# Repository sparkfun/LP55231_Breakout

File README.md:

SparkFun LP55231 LED Driver Breakout
========================================

[*SparkFun LP55231 LED Driver Breakout (BOB-13884)*](https://www.sparkfun.com/products/13884)

Breakout Board for the Texas Instruments LP55231 9-channel LED driver IC, with three onboard RGB LEDs.

Repository Contents
-------------------

* **/Documentation** - LP55231 data sheet.
* **/Enclosure** - Enclosure files
* **/Firmware** - Some test sketches.  For more useful sketches, please refer to the [LP55231 Arduino Library](https://github.com/sparkfun/SparkFun_LP55231_Arduino_Library)
* **/Hardware** - Eagle design files (.brd, .sch)
* **/Libraries** - work-in-progress libraries.  Release library has [its own repository](https://github.com/sparkfun/SparkFun_LP55231_Arduino_Library)
* **/Production** - Production panel files (.brd)
* **/Software** - Related software for the <PRODUCT NAME>

Documentation
--------------
* **[Library](https://github.com/sparkfun/SparkFun_LP55231_Arduino_Library)** - Arduino library for the LP55231 breakout board.
* **[Hookup Guide](https://learn.sparkfun.com/tutorials/lp55231-breakout-board-hookup-guide)** - Basic hookup guide for the LP55231 breakout.
* **[SparkFun Fritzing repo](https://github.com/sparkfun/Fritzing_Parts)** - Fritzing diagrams for SparkFun products.
* **[SparkFun 3D Model repo](https://github.com/sparkfun/3D_Models)** - 3D models of SparkFun products.
* **[SparkFun Graphical Datasheets](https://github.com/sparkfun/Graphical_Datasheets)** -Graphical Datasheets for various SparkFun products.

Product Versions
----------------
* [BOB-13884](https://www.sparkfun.com/products/13884)- Storefront page where you can purchase the LP55231 breakout board.

Version History
---------------
* [7303a14bc03e4db13bc608a852c81e9e0ca2a5a7](https://github.com/sparkfun/LP55231_Breakout/commit/7303a14bc03e4db13bc608a852c81e9e0ca2a5a7) - Initial release version.

License Information
-------------------

This product is _**open source**_!

Please review the LICENSE.md file for license information.

If you have any questions or concerns on licensing, please contact techsupport@sparkfun.com.

Distributed as-is; no warranty is given.

- Your friends at SparkFun.

_<COLLABORATION CREDIT>_

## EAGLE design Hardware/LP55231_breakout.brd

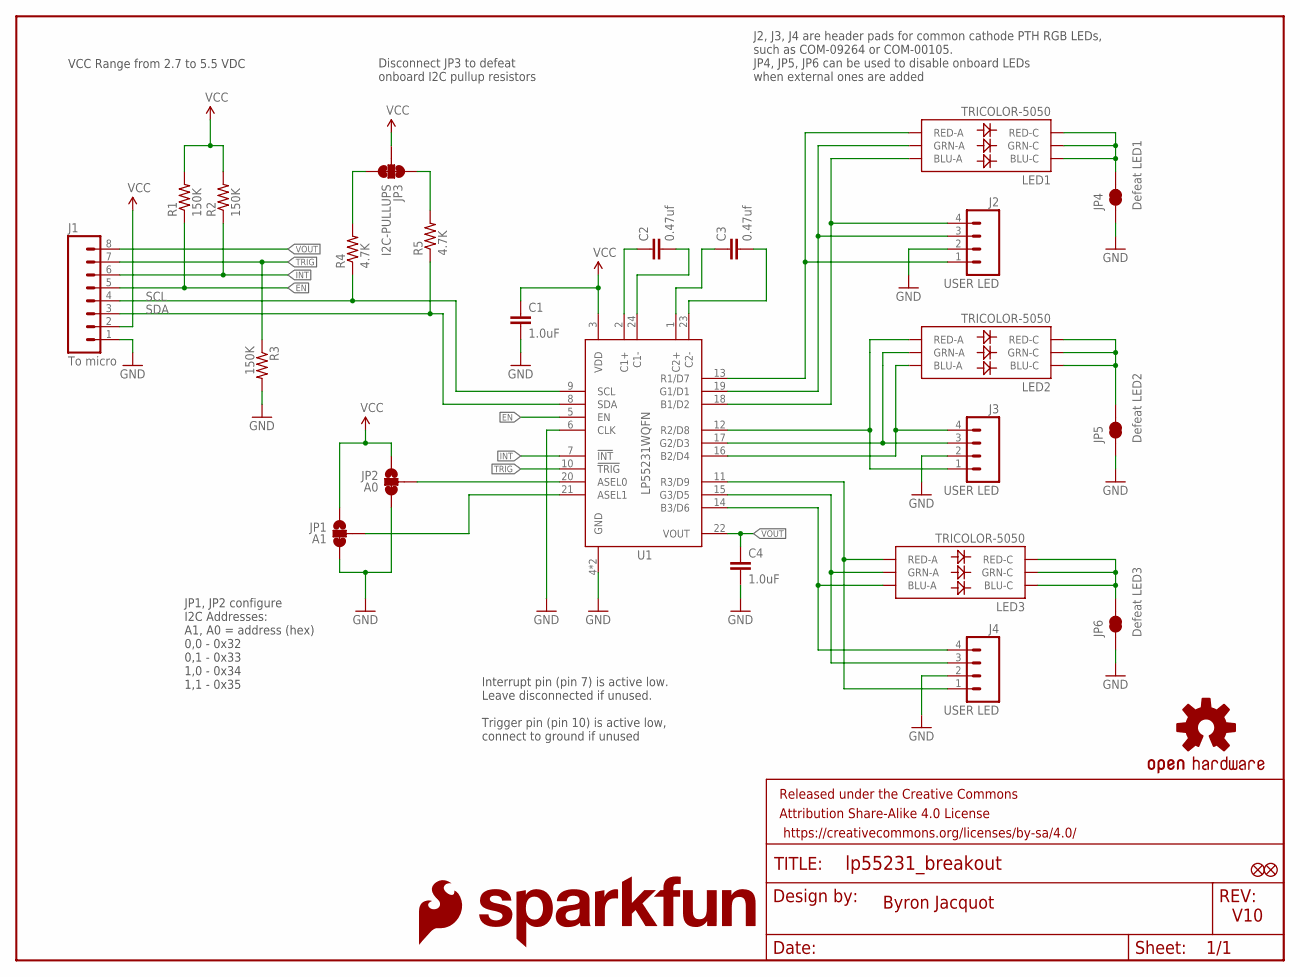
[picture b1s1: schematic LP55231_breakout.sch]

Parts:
C1, C4: 1.0uF; 0603-CAP
C2, C3: 0.47uf; 0603-CAP
FD1, FD2: FIDUCIALUFIDUCIAL; MICRO-FIDUCIAL
FRAME1: FRAME-LETTER; CREATIVE_COMMONS
J1: To micro; 1X08_NO_SILK
J2, J3, J4: USER LED; 1X04_NO_SILK_ALL_ROUND
JP1: A1; PAD-JUMPER-3-2OF3_NC_BY_TRACE_YES_SILK_FULL_BOX
JP2: A0; PAD-JUMPER-3-2OF3_NC_BY_TRACE_YES_SILK_FULL_BOX
JP3: I2C-PULLUPS; PAD-JUMPER-3-3OF3_NC_BY_TRACE_YES_SILK_FULL_BOX
JP4: Defeat LED1; PAD-JUMPER-2-NC_BY_TRACE_NO_SILK
JP5: Defeat LED2; PAD-JUMPER-2-NC_BY_TRACE_NO_SILK
JP6: Defeat LED3; PAD-JUMPER-2-NC_BY_TRACE_NO_SILK
LED1, LED2, LED3: TRICOLOR-5050; LED-TRICOLOR-5050
LOGO1: SFE_LOGO_FLAME.1_INCH; SFE_LOGO_FLAME_.1
LOGO2: SFE_LOGO_NAME.1_INCH; SFE_LOGO_NAME_.1
LOGO3: OSHW-LOGOS; OSHW-LOGO-S
R1, R2, R3: 150K; 0603-RES
R4, R5: 4.7K; 0603-RES
U1: LP55231WQFN; WQFN-24

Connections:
ADDR0: JP2.2, U1.20 (ASEL0)
ADDR1: JP1.2, U1.21 (ASEL1)
B1: J2.4, LED1.3 (BLU-A), U1.18 (B1/D2)
B2: J3.4, LED2.3 (BLU-A), U1.16 (B2/D4)
B3: J4.4, LED3.3 (BLU-A), U1.14 (B3/D6)
EN: J1.5, R1.1, U1.5 (EN)
G1: J2.3, LED1.1 (GRN-A), U1.19 (G1/D1)
G2: J3.3, LED2.1 (GRN-A), U1.17 (G2/D3)
G3: J4.3, LED3.1 (GRN-A), U1.15 (G3/D5)
GND: C1.2, C4.2, J1.1, J2.2, J3.2, J4.2, JP1.3, JP2.3, JP4.1, JP5.1, JP6.1, R3.2, U1.4 (GND), U1.6 (CLK), U1.EP (GND)
INT: J1.6, R2.1, U1.7 (!INT)
unnamed: JP6.2, LED3.4 (BLU-C), LED3.5 (RED-C), LED3.6 (GRN-C)
unnamed: JP5.2, LED2.4 (BLU-C), LED2.5 (RED-C), LED2.6 (GRN-C)
unnamed: JP4.2, LED1.4 (BLU-C), LED1.5 (RED-C), LED1.6 (GRN-C)
unnamed: C2.1, U1.2 (C1+)
unnamed: C2.2, U1.24 (C1-)
unnamed: C3.1, U1.1 (C2+)
unnamed: C3.2, U1.23 (C2-)
unnamed: JP3.1, R5.2
unnamed: JP3.3, R4.2
R1: J2.1, LED1.2 (RED-A), U1.13 (R1/D7)
R2: J3.1, LED2.2 (RED-A), U1.12 (R2/D8)
R3: J4.1, LED3.2 (RED-A), U1.11 (R3/D9)
SCL: J1.4, R4.1, U1.9 (SCL)
SDA: J1.3, R5.1, U1.8 (SDA)
TRIG: J1.7, R3.1, U1.10 (!TRIG)
VCC: C1.1, J1.2, JP1.1, JP2.1, JP3.2, R1.2, R2.2, U1.3 (VDD)
VOUT: C4.1, J1.8, U1.22 (VOUT)

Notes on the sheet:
Byron Jacquot
V10
VCC Range from 2.7 to 5.5 VDC
JP1, JP2 configure I2C Addresses: A1, A0 = address (hex) 0,0 - 0x32 0,1 - 0x33 1,0 - 0x34 1,1 - 0x35
J2, J3, J4 are header pads for common cathode PTH RGB LEDs, such as COM-09264 or COM-00105. JP4, JP5, JP6 can be used to disable onboard LEDs when external ones are added
Disconnect JP3 to defeat onboard I2C pullup resistors
Interrupt pin (pin 7) is active low. Leave disconnected if unused. Trigger pin (pin 10) is active low, connect to ground if unused

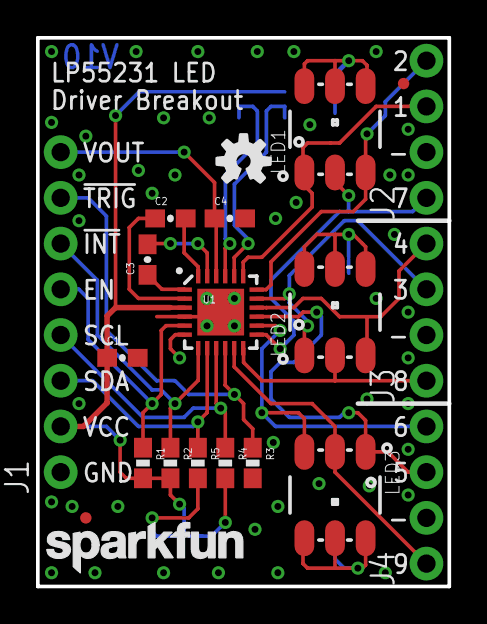
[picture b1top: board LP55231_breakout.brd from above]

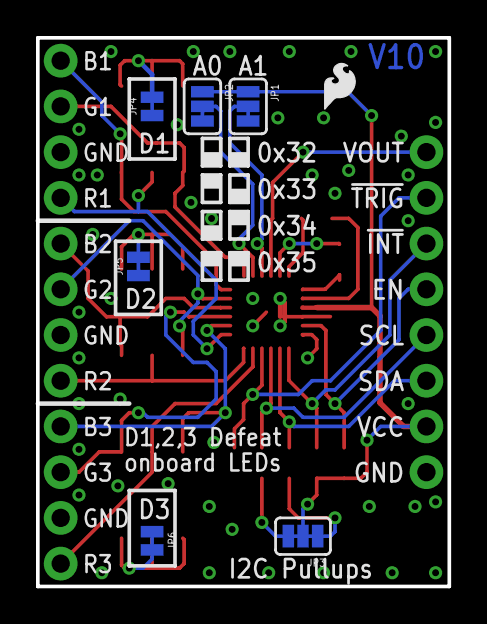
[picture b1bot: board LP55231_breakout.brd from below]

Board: 4 copper layers, 22.9 x 30.5 mm, 29 parts (7 on the bottom side), 28 nets.

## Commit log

2016-03-14 Adding repo boilerplate.
2016-03-15 Initial design files.
    Library, schem and PCB, all WIP.
2016-03-24 PCB Work in progress.
2016-03-25 Incremental PCB routing checkin.
    Eagle crashed and I'm paranoid now.
2016-03-25 Routing approaching completion.
2016-03-31 Prepping for review.
    BOM created, checklist scrubbed.
2016-04-04 Straight out of QFN.
    Fewer bends & kinks.
2016-04-04 Fixing review issues.
    -Fiducial moved from under silk.
    -Swapped numbering of LED's 2 & 3.
2016-04-27 Adding datasheet and test sketch.
2016-04-27 Adding a note for I2C r/w info.
2016-04-28 Hardware is starting to talk.
    Not sophisticated, but minimally functional.
2016-04-28 More success...
    ...I've got a little program running in one of the execution engines.
2016-04-28 Execution engine & output mapping
    cumbersome but functional!
2016-05-03 Working on library class
2016-05-04 Incremental changes.
    Adding software library features to support hardware testing.
    Trigger and interrupt pins are working.
2016-05-06 Updates to PCB after testing.
    Preparing for second round of prototypes.
2016-05-09 Updates after group review.
    Addressing things in issue #3:
    -bump version number
    -Add silk indicating flooded/empty configuration on A0/A1
    -space out passives on front (check tkeepout)
    -remove extra junction dot between 150k res and Vcc on schematic
2016-05-10 Checklist updates for proto round 2.
2016-05-11 Checklist review issues
    Numbering of jumpers vs. comments got mismatched.
    Now fixed.
2016-06-15 Fixing RGB assignments of first LED.
2016-06-21 Rolling version number
    From V02 to V03.
2016-06-22 Changes post-review.
    "G" becomes "-", to prevent confusion with "6".
    Angle voliation inside LED pad remedied.
2016-06-24 Clarifying one schematic note.
2016-07-29 Adding some hardware test sketches.
2016-08-05 Adding micro->driver trigger example.
2016-08-16 Adding sketches for Interrupt and output triggering.
2016-08-16 Adding sample sketch example of bidirectional trigger.
    Got the pin direction question answered.
    There's an external pull down that tugs the line when the internal pulup
    gets defeated.
2016-08-17 Adding start on Arduino Library...
    Basics are working, but parallel engines, program verification are not.
2016-08-18 Program verification is working.
    On a single page, at least.
    Setting PC is still problematic.
2016-08-18 Adding multi-page write/verify.
2016-08-19 Making updates after group & checklist reviews.
    Rolling version # to V10.
2016-08-22 Improvements to parallel engines.
    Takes careful manipulation of memory.
    PC & branches are done relative to program entry point, not absolute
    instruction location.
2016-08-23 More integration tests
    Temperature reading
    ADC for outputs and voltages.
2016-08-25 Adding auto-larson-scanner
    Found & fixed pervasive error in page programming.
    Added larson scanner with large mapping table.
2016-10-06 Reorganizing libraries a bit.
    Adding multi-page programming, and Int-to-GPO access.
2016-10-06 Adding interrupt-to-GPO override example.
2016-10-06 Adding example for testing teo chips on same bus
2016-10-06 Fixing page accesses to program memory
2016-10-06 Touchups to input-trigger example.
    It'd fallen behind the newer library updates.
2016-10-06 Similar updates to output trigger example
    Bringing in latest execution engine knowledge.
2016-11-04 Updating readme to make repo public.
2016-11-04 One more readme tweak.

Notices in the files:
parts and their libraries:
SparkFun-Aesthetics: Licensing: Creative Commons ShareAlike 4.0 International - https://creativecommons.org/licenses/by-sa/4.0
SparkFun-Aesthetics: Released under the Creative Commons Attribution Share-Alike 4.0 License
SparkFun-Aesthetics: https://creativecommons.org/licenses/by-sa/4.0
